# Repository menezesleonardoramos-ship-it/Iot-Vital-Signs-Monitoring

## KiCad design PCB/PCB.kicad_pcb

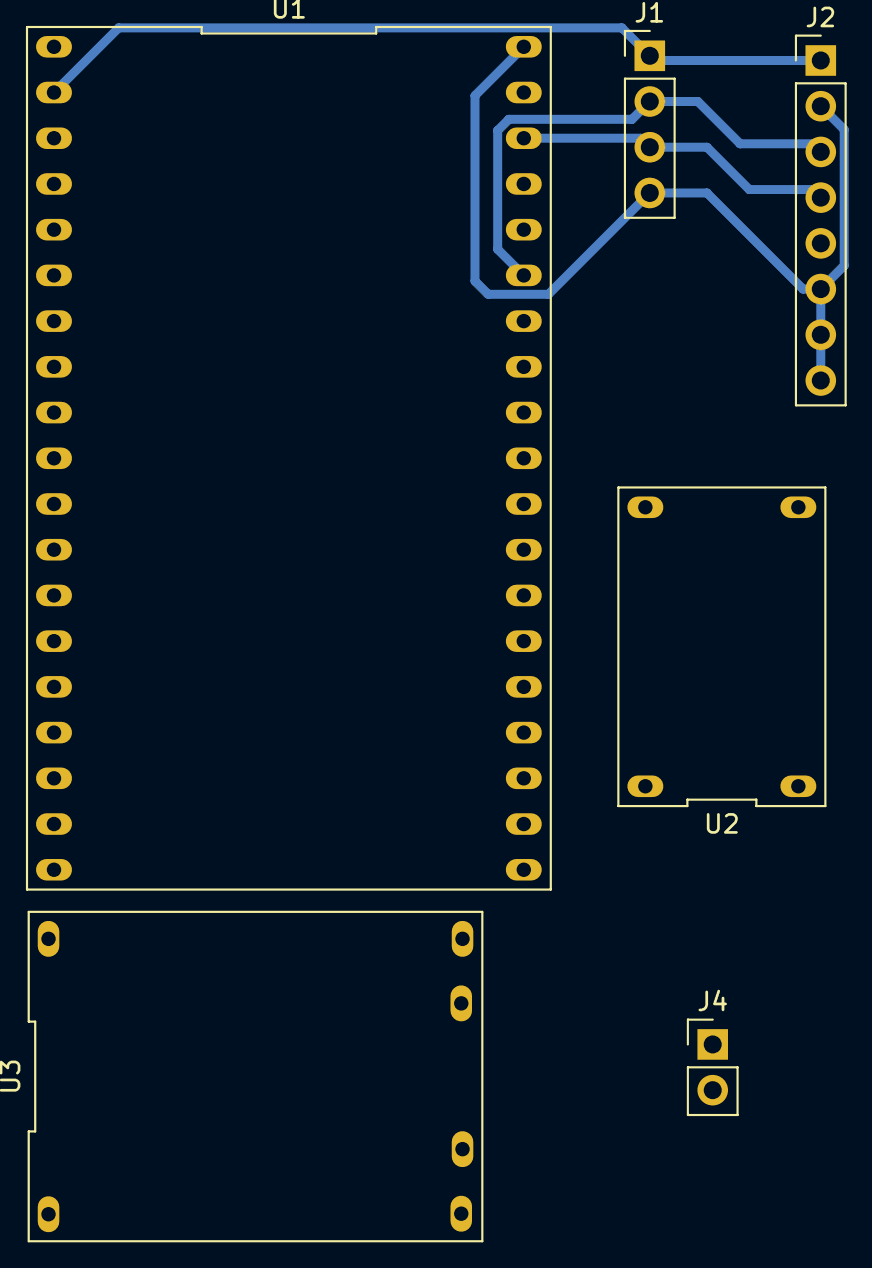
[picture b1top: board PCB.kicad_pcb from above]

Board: 2 copper layers, 6 parts (0 on the bottom side), 8 nets.

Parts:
J1: MAX105; PinHeader_1x04_P2.54mm_Vertical
J2: MAX30205; PinHeader_1x08_P2.54mm_Vertical
J4: Conn_01x02; PinHeader_1x02_P2.54mm_Vertical
U1: ESP32-WROOM-32D; esp32 wroom
U2: DSN_MINI_360
U3: BMS

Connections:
unnamed: J1.1, J2.1, U1.2 (VDD), U2.3 (OUT+)
unnamed: J1.2, J2.3, U1.33 (IO21)
unnamed: J1.3, J2.4, U1.36 (IO22)
unnamed: J1.4, J2.2, J2.6, J2.7, J2.8, U1.1 (GND), U1.15 (GND), U1.38 (GND), U2.4 (OUT-)
unnamed: J4.1, U3.5 (B+)
unnamed: J4.2, U3.6 (B-)
unnamed: U2.1 (IN+), U3.3 (OUT+)
unnamed: U2.2 (IN-), U3.4 (OUT-)

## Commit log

2026-01-14 Projeto Integradora
2026-01-14 Organizando Repositório
2026-01-14 Organizando Pastas
2026-01-14 Adicionando Códito MAX30102
2026-01-14 Novo código para sensores junto com firebase
2026-01-14 Codigo funcionando o BPM
2026-01-14 Adicionando corpo código firebase sensor (não funcional)
2026-01-14 Codigo funcionando, falta apenas temp
2026-01-14 Add health monitoring system with Firebase integration
    This file implements a health monitoring system using MAX30105 and MAX30205 sensors, displaying heart rate, SpO2, and temperature on an OLED screen, and sending data to Firebase.
2026-01-14 Tudo funcional
2026-01-14 Movendo Definitivos para teste (conseguiu código certo)
2026-01-14 Codigo funcionando todos os sensores
2026-01-14 Add MAX30105 and MAX30205 sensor integration
2026-01-14 Código tudo funcionando menos temperatura
2026-01-14 Mudança código teste_final1.txt funcional BPM e SpO2
2026-01-14 teste_final2.txt funcionando quase tudo menos OLED
2026-01-14 Pasta com todos os códigos finais / teste_finais3 com todos sensores funcionando(SpO2 +/-)
2026-01-14 Ajuste dos sensores
2026-01-14 Todos os sensores funcionando mas sem histórico
2026-01-14 Codigo funcional
2026-02-04 corrigindo pasta
2026-02-04 modificando código original
2026-02-04 Create modificando_site
2026-02-05 Descrevendo código
2026-02-05 Atualizando código
2026-02-05 Create MonitorMed dashboard for patient monitoring
    Added a new HTML dashboard for MonitorMed with patient monitoring features, including heart rate, oxygen levels, and temperature. Integrated Firebase for real-time data updates.
